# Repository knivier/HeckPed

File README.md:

# HeckPed

The Hack Pad journey. Make sure you read the entire README and all its notes, it's all chronological (it's like a Journalplzreadme.md)

### BOM

* Two capacitors of type 0.1uf (I will be purchasing this, no biggie), it's coming in this set: https://www.amazon.com/ALLECIN-Electrolytic-Capacitor-Assortment-Kit/dp/B0C1VBXCQM?sr=8-2
* Four Switches of type Cherry Red 45cn
* Four Keycaps (i dont care which type as long as they are White/Black and semi low profile [not chonky])
* Two LED Diodes
* One printed part (CAD list)
* 1 PCB
* 1x XIAO RP2040

No top panel, it'd be easy but I want to see the electronics anyways cuz it's cool. I might think about a clear panel in the future which is why I kept the screws.

6/30/2025 Updates:

Notes: The decoupling capacitors are in the correct format, I have checked with multiple sources (no, I did not check with AI, thanks for asking). 

I have size checked the PCB to the CAD and created a complete CADout of the entire design with good amounts of breathing room and a top panel. The PCB now runs the DRC checks with no errors (ignore the footprint warnings, those do not impact anything and I have checked them with the capacitors I will be using, no impact whatsoever). 

I updated the PCB here, THANK YOU MEDDY. Well WE

There is also a top part of the CAD. There are 3 parts in the CAD directory.
Here's the complete part:

There is also a production folder with Gerber and drill files, CAD case designs (top and bottom separated, no CADOUT inside production for PCB) and firmware customized to my use case.

## VERY IMPORTANT NOTE 
Logan made me put this here

I will be drilling the top plate into the bottom plate as I've had issues with wiggling in the past. Drilling will be way more stable.

I will also be elevating the XIAO slightly so it fits with the keyboard switch there.

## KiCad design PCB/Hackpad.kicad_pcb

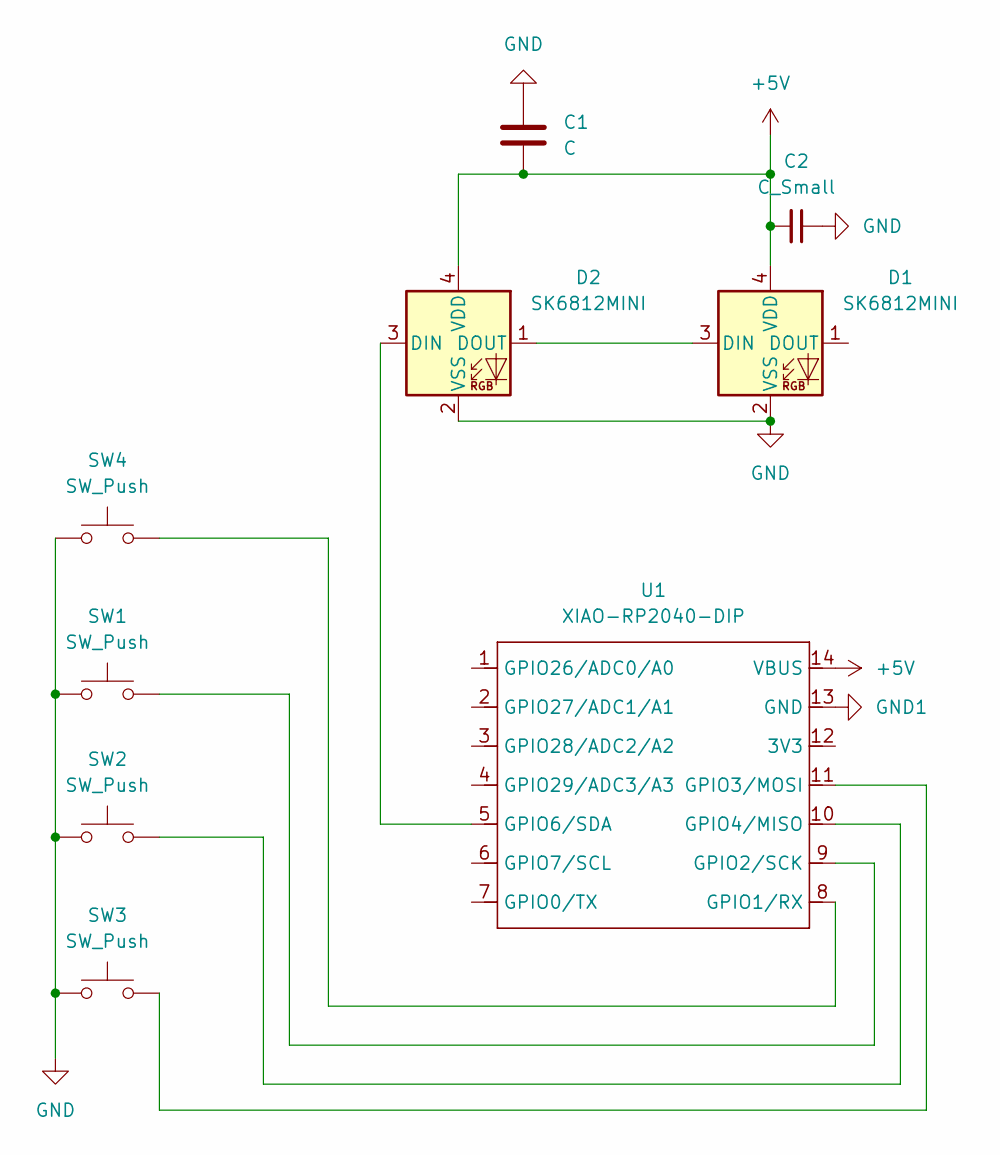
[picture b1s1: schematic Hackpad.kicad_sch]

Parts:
C1: C; C_Axial_L3.8mm_D2.6mm_P7.50mm_Horizontal
C2: C_Small; C_Axial_L3.8mm_D2.6mm_P7.50mm_Horizontal
D1, D2: SK6812MINI; LED_SK6812MINI_PLCC4_3.5x3.5mm_P1.75mm
SW1, SW2, SW3, SW4: SW_Push; SW_Cherry_MX_1.00u_PCB
U1: XIAO-RP2040-DIP

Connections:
+5V: C1.2, C2.2, D1.4 (VDD), D2.4 (VDD), U1.14 (VBUS)
GND: C1.1, C2.1, D1.2 (VSS), D2.2 (VSS), SW1.1, SW2.1, SW3.1, SW4.1
GND1: U1.13 (GND)
unnamed: D1.3 (DIN), D2.1 (DOUT)
unnamed: D2.3 (DIN), U1.5 (GPIO6/SDA)
unnamed: SW4.2, U1.8 (GPIO1/RX)
unnamed: SW1.2, U1.9 (GPIO2/SCK)
unnamed: SW3.2, U1.11 (GPIO3/MOSI)
unnamed: SW2.2, U1.10 (GPIO4/MISO)

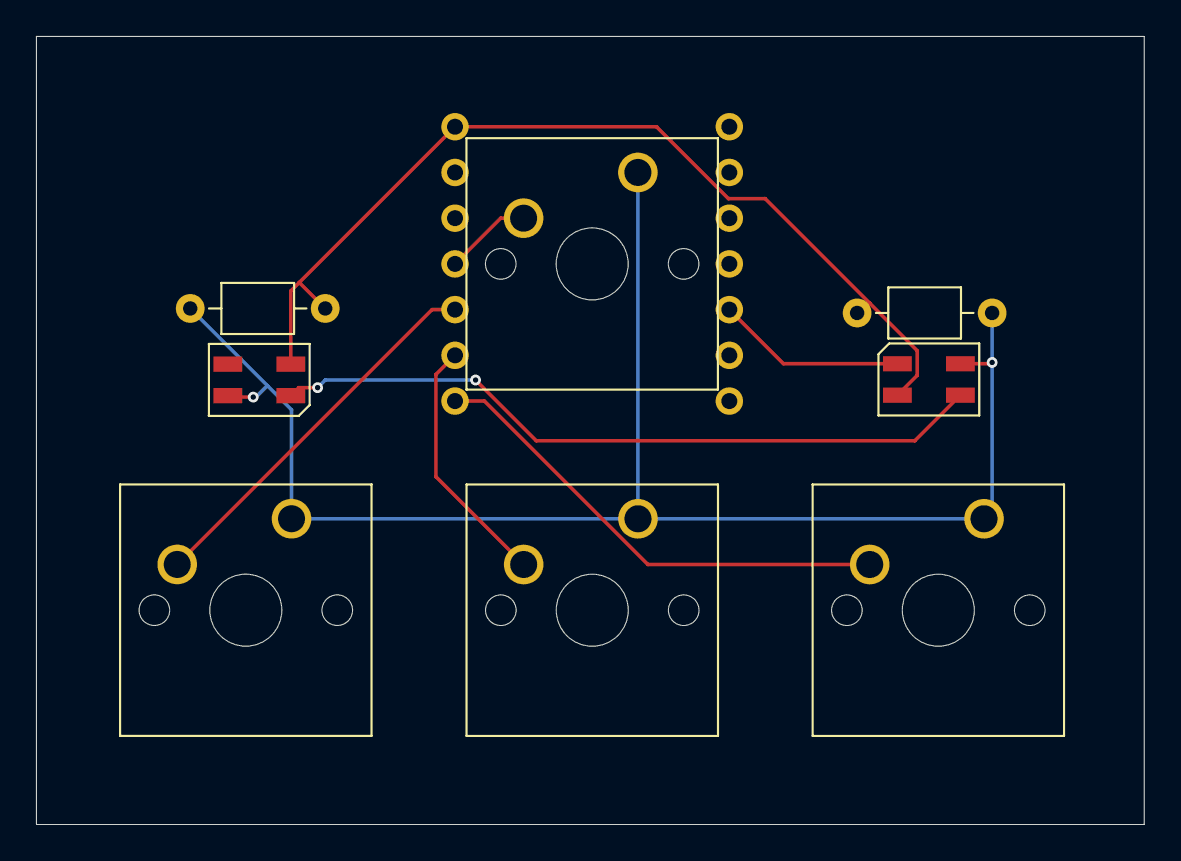
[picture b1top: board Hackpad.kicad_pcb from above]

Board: 2 copper layers, 61.5 x 43.8 mm, 9 parts (1 on the bottom side), 8 nets.

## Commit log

2025-06-26 pcb design stuff
2025-06-26 wiring better
2025-06-27 lotta stuff
2025-06-29 attempted changes
2025-07-01 fixed a lottta errors-ty meddy
2025-07-01 Completed heckped
2025-07-01 autosave stuff
2025-07-01 Okay images and restructuring for logan
2025-07-01 updated notes
2025-07-01 RENAMED LAST THING IM SLEEP DEPRIVED
2025-07-01 Im too tired for ts added some pics
